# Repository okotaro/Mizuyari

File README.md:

# Mizuyari

電気回路CAD（KiCad）とマイコンファームウェアを管理するモノレポ。

## 構成

```
.
├── hardware/   # KiCadプロジェクト（回路図・基板設計）
├── firmware/   # マイコンファームウェア
└── docs/       # 設計資料・ドキュメント
```

各ディレクトリの詳細は `hardware/README.md` / `firmware/README.md` を参照。

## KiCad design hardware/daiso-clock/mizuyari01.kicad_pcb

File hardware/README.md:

# hardware

KiCadプロジェクトを格納するディレクトリ。

プロジェクトごとにサブディレクトリを作成する想定:

```
hardware/
└── <project-name>/
    ├── <project-name>.kicad_pro
    ├── <project-name>.kicad_sch
    ├── <project-name>.kicad_pcb
    └── ...
```

ビルド生成物（`*.bak`, `fp-info-cache`, `*-backups/` 等）はコミットしない。

## 設計レビュー

回路図・基板は Claude Code に直接読ませてレビューできる。
スクリーンショットではなく設計データ（`.kicad_sch` / `.kicad_pcb` / ガーバー）を解析する。

```
hardware/daiso-clock/ の回路図と基板をレビューして
```

解析結果は `analysis/` に残る（再生成できるためコミットしない）。
仕組みと注意点は `.kiro/steering/tech.md` の「設計レビュー」を参照。

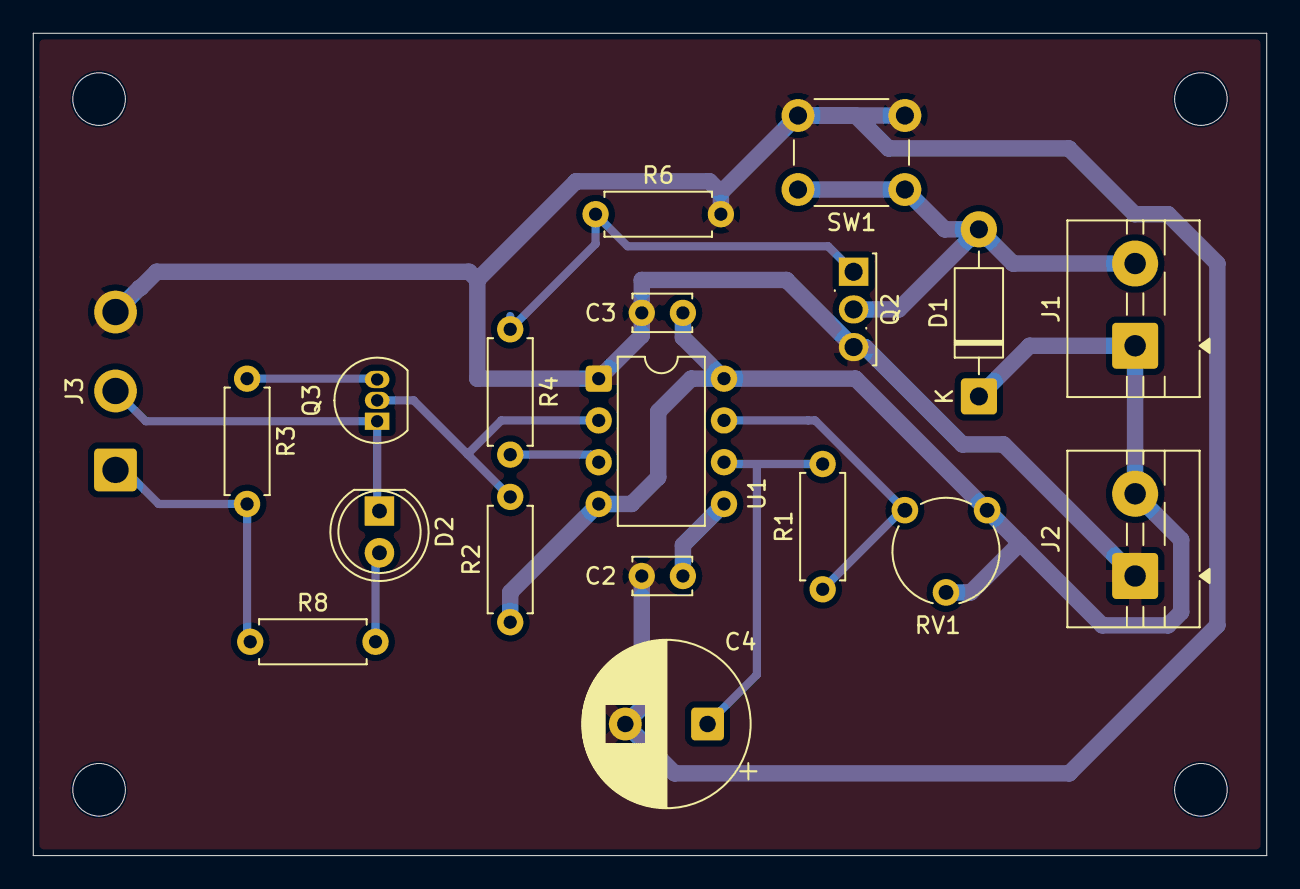
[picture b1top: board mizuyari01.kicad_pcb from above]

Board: 2 copper layers, 75.0 x 50.0 mm, 23 parts (0 on the bottom side), 13 nets.

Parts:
C2, C3: 0.1u; C_Disc_D3.4mm_W2.1mm_P2.50mm
C4: 470u; CP_Radial_D10.0mm_P5.00mm
D1: D_Schottky; D_DO-41_SOD81_P10.16mm_Horizontal
D2: LED; LED_D5.0mm
H1, H2, H3, H4: MountingHole; MountingHole_3.2mm_M3
J1, J2: Screw_Terminal_01x02; TerminalBlock_MaiXu_MX126-5.0-02P_1x02_P5.00mm
J3: Conn_01x03_Pin; SolderWire-0.75sqmm_1x03_P4.8mm_D1.25mm_OD2.3mm
Q2: Q_NMOS_GDS; TO-251-3_Vertical
Q3: 2SC1815; TO-92_Inline
R1: 2.2k; R_Axial_DIN0207_L6.3mm_D2.5mm_P7.62mm_Horizontal
R2, R3, R6: 10k; R_Axial_DIN0207_L6.3mm_D2.5mm_P7.62mm_Horizontal
R4: 100; R_Axial_DIN0207_L6.3mm_D2.5mm_P7.62mm_Horizontal
R8: 330; R_Axial_DIN0207_L6.3mm_D2.5mm_P7.62mm_Horizontal
RV1: 10k; Potentiometer_Piher_PT-6-V_Vertical
SW1: SW_Push; SW_PUSH_6mm
U1: NE555P; DIP-8_W7.62mm

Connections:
ALM: D2.1 (K), J3.2, Q3.1 (E)
GND: C2.2, C3.2, C4.2, J2.1, J3.3, Q2.3 (S), R6.2, SW1.2, U1.1 (GND)
MTR-N: D1.2 (A), J1.2, Q2.2 (D), SW1.1
unnamed: D2.2 (A), R8.2
unnamed: Q2.1 (G), R4.1, R6.1
unnamed: Q3.3 (B), R3.1
unnamed: Q3.2 (C), R2.2, U1.2 (TRIG)
unnamed: C2.1, U1.5 (CONT)
unnamed: R1.1, RV1.1, U1.7 (DISCH)
unnamed: C4.1, R1.2, U1.6 (THRES)
VCC: C3.1, D1.1 (K), J1.1, J2.2, R2.1, RV1.2, RV1.3, U1.4 (~RST), U1.8 (VCC)
V_WATCH: J3.1, R3.2, R8.1
tmout: R4.2, U1.3 (OUT)
